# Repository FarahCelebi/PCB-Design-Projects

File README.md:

PCB Design Projects

A set of PCB designs built in KiCad, covering circuit fundamentals through to a complete USB-C powered environmental sensor system. Each project includes the full schematic, PCB layout, and the design reasoning behind key decisions — component selection, power regulation, signal integrity, and manufacturability.

Skills demonstrated

- Schematic capture, ERC, and footprint assignment
- PCB layout, routing, and Design Rules Checking (DRC)
- Current-limiting and Ohm's law-based component selection
- Decoupling capacitor strategy and power supply design (LDO regulation)
- Multi-layer (4-layer) stack-ups with dedicated GND/power planes
- I2C bus design, addressing, and pull-up resistor sizing
- USB-C power delivery, ESD protection, and differential pair routing
- Copper pours, thermal relief, and controlled-impedance routing
- Design for Manufacture (DFM): trace width selection, silkscreen clearance, panelization-aware board outlines
- Gerber generation and verification for fabrication

Projects
| # | Project | Description |
|---|---------|-------------|
| 01 | [LED Blink Circuit](./01-Led-Blink-Circuit) | Current-limited LED driver circuit with calculated resistor values for two different LED forward voltages. |
| 02 | [ATtiny85 Microcontroller Board](./02-ATtiny85-Microcontroller) | Minimal ATtiny85 breakout with a proper reset circuit, decoupling, and a ground plane, on a 2-layer board. |
| 03 | [AMS1117 Power Supply](./03-AMS1117-Power-Supply) | 5V-to-3.3V regulated power supply with proper input/output decoupling, built on a 4-layer stackup with dedicated GND/power planes. |
| 04 | [BME280 I2C Sensor Board](./04-BME280-I2C-Sensor) | Self-contained sensor module with onboard 5V-to-3.3V regulation, an ATtiny85, and a BME280 environmental sensor over I2C. |
| 05 | [USB-C Power Board](./05-USB-C-Power-Board) | USB-C input with ESD protection, CC detection, differential pair routing, and 3.3V regulation. |
| 06 | [IoT Environmental Monitor (Capstone)](./06-IoT-Environmental-Monitor) | Full system: USB-C input with ESD protection, onboard power regulation, an ATtiny85, and a BME280 sensor. Designed, fabricated, and assembled. |

Tools

- KiCad (schematic capture, PCB layout, DRC/ERC)

About this repository

Each project folder contains:
- A README with the design brief, schematic, PCB layout, and key decisions
- Schematic and PCB screenshots
- KiCad source files

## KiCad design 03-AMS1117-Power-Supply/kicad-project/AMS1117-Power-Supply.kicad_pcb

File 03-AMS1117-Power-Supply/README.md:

# AMS1117 Power Supply

A 5V-to-3.3V linear regulator board with full input/output decoupling,
built on a 4-layer stackup with dedicated ground and power planes.

## Schematic

## PCB Layout

## Design notes

- **Regulator:** AMS1117-3.3, a fixed 3.3V LDO. Input and output decoupling
  follow the datasheet's recommended pairing — a 10uF bulk capacitor for
  transient current demand alongside a 100nF capacitor for high-frequency
  noise, on both the input and output rails
- **Connectors:** J1 (input) and J2 (output) sit on opposite sides of the
  board, with the regulator in between — keeping the power path visually
  traceable left to right
- **PWR_FLAG:** placed on the +3.3V output rail and on GND, since both are
  externally driven/sourced rather than generated on this sheet, which
  satisfies KiCad's ERC for power rails with no visible source

## Stackup

This board uses a 4-layer stackup:

| Layer | Use |
|-------|-----|
| F.Cu | Component placement, signal/power routing |
| In1.Cu | Dedicated GND plane (solid pour) |
| In2.Cu | Dedicated power plane (solid pour)|
| B.Cu | Unused on this board — all routing fit on F.Cu |

A solid ground plane on an inner layer gives every trace on F.Cu a continuous,
low-impedance return path directly beneath it, which reduces EMI and noise
coupling compared to routing GND as traces on a single layer. For a simple
linear regulator like this, 2 layers would work fine electrically — this
board uses 4 specifically to establish and verify the stackup configuration,
via placement, and inner-layer pour workflow in KiCad.

## Manufacturing

- SMD throughout (SOT-223 regulator, 0805/0402 passives) for compact assembly
- Passed DRC with 0 violations, 0 unconnected nets
- Inner layer fills set to solid (not thermal relief) on small SMD pads

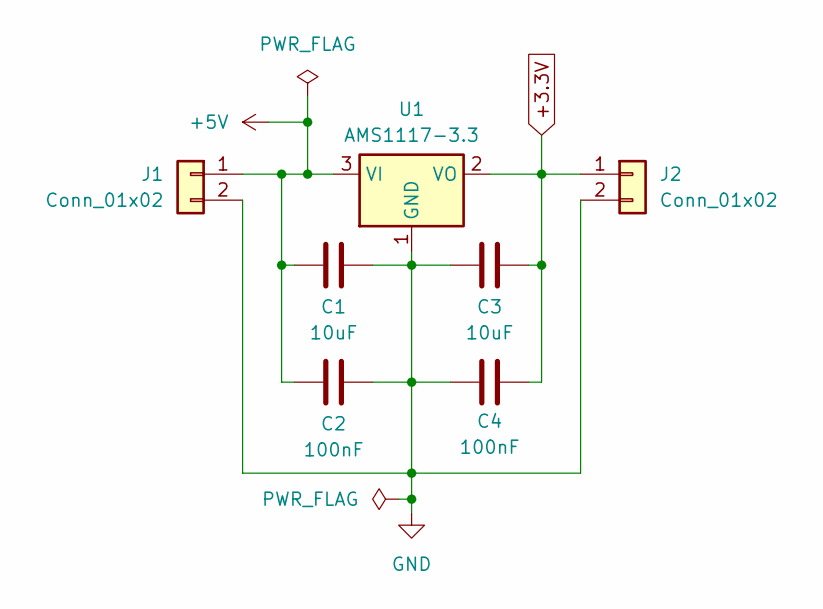
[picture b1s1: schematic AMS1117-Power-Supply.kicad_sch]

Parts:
C1, C3: 10uF; C_0805_2012Metric
C2, C4: 100nF; C_0402_1005Metric
J1, J2: Conn_01x02; PinHeader_1x02_P2.54mm_Vertical
U1: AMS1117-3.3; SOT-223-3_TabPin2

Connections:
+3.3V: C3.2, C4.2, J2.1, U1.2 (VO)
+5V: C1.2, C2.2, J1.1, U1.3 (VI)
GND: C1.1, C2.1, C3.1, C4.1, J1.2, J2.2, U1.1 (GND)

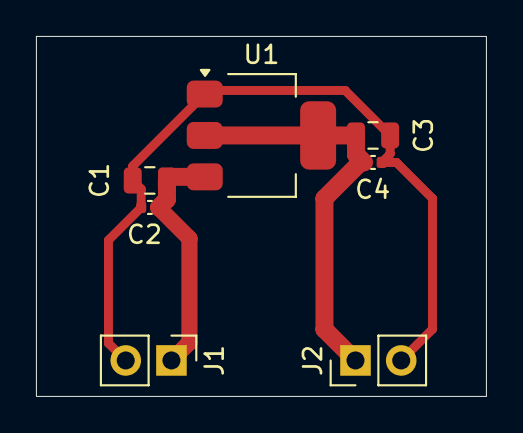
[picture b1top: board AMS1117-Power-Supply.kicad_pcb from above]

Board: 4 copper layers, 25.0 x 20.0 mm, 7 parts (0 on the bottom side), 3 nets.

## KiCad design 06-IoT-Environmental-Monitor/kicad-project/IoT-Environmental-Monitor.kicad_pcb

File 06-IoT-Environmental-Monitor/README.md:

# IoT Environmental Monitor

A complete, USB-C powered environmental sensor system: USB-C input with ESD
protection, onboard 3.3V regulation, an ATtiny85 microcontroller, and a
BME280 sensor reading temperature, humidity, and pressure over I2C. 

## Schematic

## PCB Layout

## Design notes

This board integrates four functional stages into one system:

**USB-C input + ESD:** the connector's CC1/CC2 pins are each pulled to GND
through a 5.1kΩ resistor, the minimum circuit needed for the board to be
recognized as a power sink and offered 5V. A USBLC6-2SC6 sits within a few
millimeters of the connector, clamping any electrostatic discharge spike
before it reaches the rest of the circuit. D+/D- run as a length- and
width-matched pair from the connector to the ESD IC.

**Power supply:** an AMS1117-3.3 regulates the incoming VBUS (5V) down to
3.3V, with standard input/output decoupling (10uF + 100nF on each side).

**ATtiny85 + I2C:** the standard MCU support circuit — 100nF decoupling, a
10kΩ RESET pull-up with a manual reset button, and 4.7kΩ pull-ups on the I2C
bus (SDA/SCL).

**BME280 sensor:** SDO is tied to GND through a 10kΩ resistor (setting the
I2C address to 0x76, per the datasheet's recommendation over a direct tie),
CSB is held high to select I2C mode over SPI, and VDD/VDDIO share the 3.3V
rail.

This is the same sensor circuit as the [BME280 I2C Sensor
Board](../04-bme280-i2c-sensor), with one key difference: that board only
accepts a 5V input on a generic 2-pin connector, while this board adds a full
USB-C input stage with CC detection and ESD protection — the difference
between a bench prototype and a board that could plug into any USB charger
or computer port.

## Layout

- Left-to-right signal flow: USB-C input → power regulation → ATtiny85 → BME280
- ESD protection IC and CC pull-downs clustered tightly around the USB-C
  connector
- D+/D- routed as a matched differential pair with no vias
- BME280 placed away from the regulator to avoid heat affecting readings
- Rectangular board outline sized to fit components with margin, keeping the
  board panelization-friendly (straight edges, no cutouts)

## Manufacturing

- 2-layer board, GND copper pour on the front copper layer
- Passed DRC with 0 violations, 0 unconnected nets

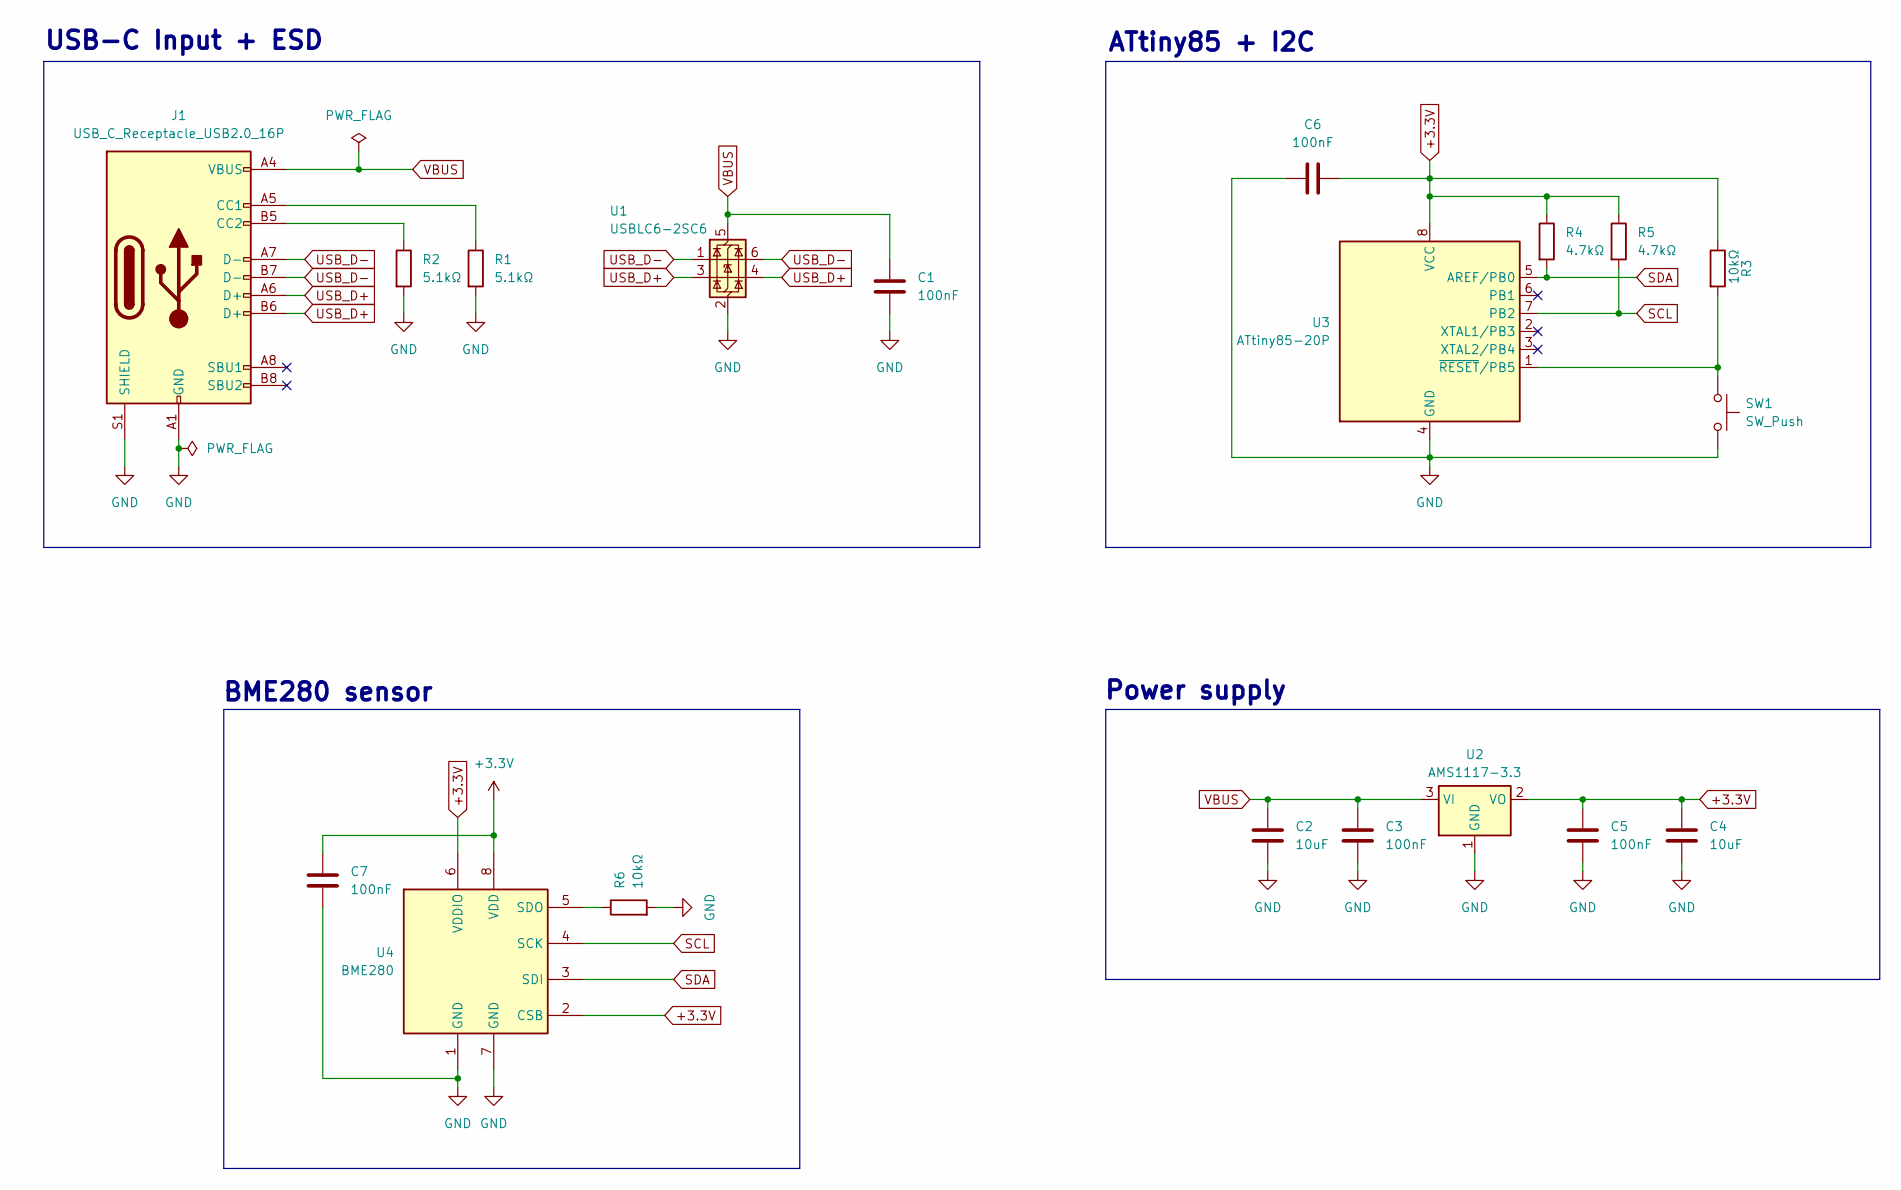
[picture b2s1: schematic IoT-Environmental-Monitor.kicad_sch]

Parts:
C1, C3, C5, C6, C7: 100nF; C_0402_1005Metric
C2, C4: 10uF; C_0805_2012Metric
J1: USB_C_Receptacle_USB2.0_16P; USB_C_Receptacle_HRO_TYPE-C-31-M-12
R1, R2: 5.1kΩ; R_0402_1005Metric
R3, R6: 10kΩ; R_0402_1005Metric
R4, R5: 4.7kΩ; R_0402_1005Metric
SW1: SW_Push; SW_PUSH_6mm
U1: USBLC6-2SC6; SOT-23-6
U2: AMS1117-3.3; SOT-223-3_TabPin2
U3: ATtiny85-20P; DIP-8_W7.62mm
U4: BME280; Bosch_LGA-8_2.5x2.5mm_P0.65mm_ClockwisePinNumbering

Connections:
+3.3V: C4.1, C5.1, C6.2, C7.1, R3.1, R4.1, R5.1, U2.2 (VO), U3.8 (VCC), U4.2 (CSB), U4.6 (VDDIO), U4.8 (VDD)
GND: C1.2, C2.2, C3.2, C4.2, C5.2, C6.1, C7.2, J1.A1 (GND), J1.A12 (GND), J1.B1 (GND), J1.B12 (GND), J1.S1 (SHIELD), R1.2, R2.2, R6.2, SW1.2, U1.2 (GND), U2.1 (GND), U3.4 (GND), U4.1 (GND), U4.7 (GND)
unnamed: J1.A5 (CC1), R1.1
unnamed: J1.B5 (CC2), R2.1
unnamed: R3.2, SW1.1, U3.1 (~RESET/PB5)
unnamed: R6.1, U4.5 (SDO)
SCL: R5.2, U3.7 (PB2), U4.4 (SCK)
SDA: R4.2, U3.5 (AREF/PB0), U4.3 (SDI)
USB_D+: J1.A6 (D+), J1.B6 (D+), U1.3 (I/O2), U1.4 (I/O2)
USB_D-: J1.A7 (D-), J1.B7 (D-), U1.1 (I/O1), U1.6 (I/O1)
VBUS: C1.1, C2.1, C3.1, J1.A4 (VBUS), J1.A9 (VBUS), J1.B4 (VBUS), J1.B9 (VBUS), U1.5 (VBUS), U2.3 (VI)

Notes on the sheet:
Power supply
BME280 sensor
ATtiny85 + I2C
USB-C Input + ESD

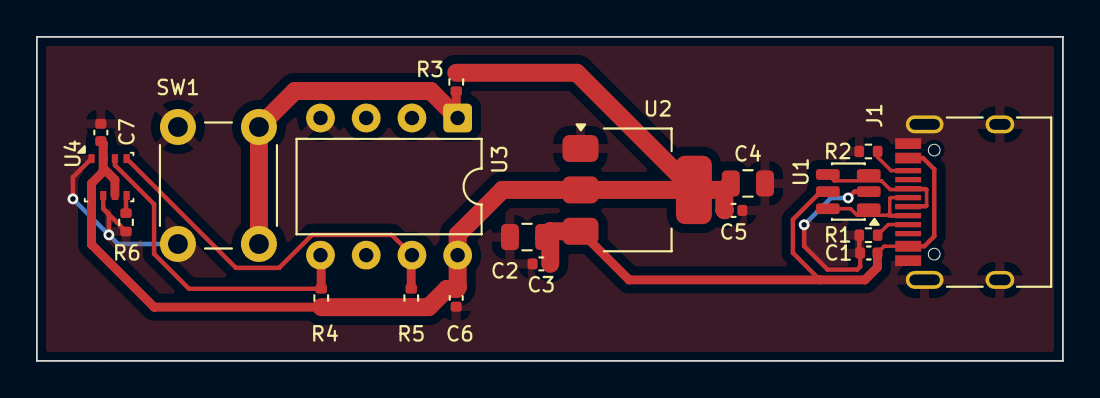
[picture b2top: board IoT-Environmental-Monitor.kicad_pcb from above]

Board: 2 copper layers, 57.0 x 18.0 mm, 19 parts (0 on the bottom side), 11 nets.

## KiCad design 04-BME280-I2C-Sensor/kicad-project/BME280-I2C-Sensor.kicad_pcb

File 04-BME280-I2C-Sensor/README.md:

# BME280 I2C Sensor Board

A self-contained environmental sensor board: takes 5V in, regulates it down
to 3.3V onboard, and reads temperature, humidity, and pressure from a BME280
over I2C via an ATtiny85.

## Schematic

## PCB Layout

## Design notes

**Power supply:** an AMS1117-3.3 regulates the 5V input down to 3.3V on board,
with the standard input/output decoupling pair (10uF + 100nF) on each side.
This makes the board self-contained — it only needs a 5V source, not a
pre-regulated 3.3V rail.

**I2C bus:** SDA and SCL run between the ATtiny85 (PB0/PB2) and the BME280,
each pulled up to 3.3V through a 4.7kΩ resistor. I2C uses open-drain
signaling, so the bus relies on these external pull-ups to return the line to
a high state — without them, both lines would float and communication would
fail.

**I2C address selection:** the BME280's SDO pin is tied to GND through a 10kΩ
resistor rather than wired directly, setting the device address to 0x76. A
direct connection works electrically the same way, but the datasheet
recommends a resistor since SDO can act as an output in some modes, and a
hard tie to GND would risk a short if that ever occurred.

**VDDIO:** the BME280 has separate VDD and VDDIO pins for its analog supply
and digital I/O supply. Both are tied to the same 3.3V rail here since the
whole board runs on a single voltage.

**Decoupling:** the ATtiny85, BME280, and AMS1117 each have capacitors placed
close to their respective power pins.

## Layout

- Three-stage left-to-right layout: power input/regulation → ATtiny85 → BME280
- BME280 placed away from the AMS1117 to avoid regulator heat skewing
  temperature readings
- Small SMD/LGA pads (BME280, 0402 passives) use solid zone connections
  rather than thermal relief spokes, since these pads are reflow-soldered in
  production and don't need the heat isolation thermal relief provides for
  hand soldering
- Some routing falls back to the back copper layer where two nets would
  otherwise cross on the front layer

## Manufacturing

- 2-layer board with GND copper pour
- Passed DRC with 0 violations, 0 unconnected nets

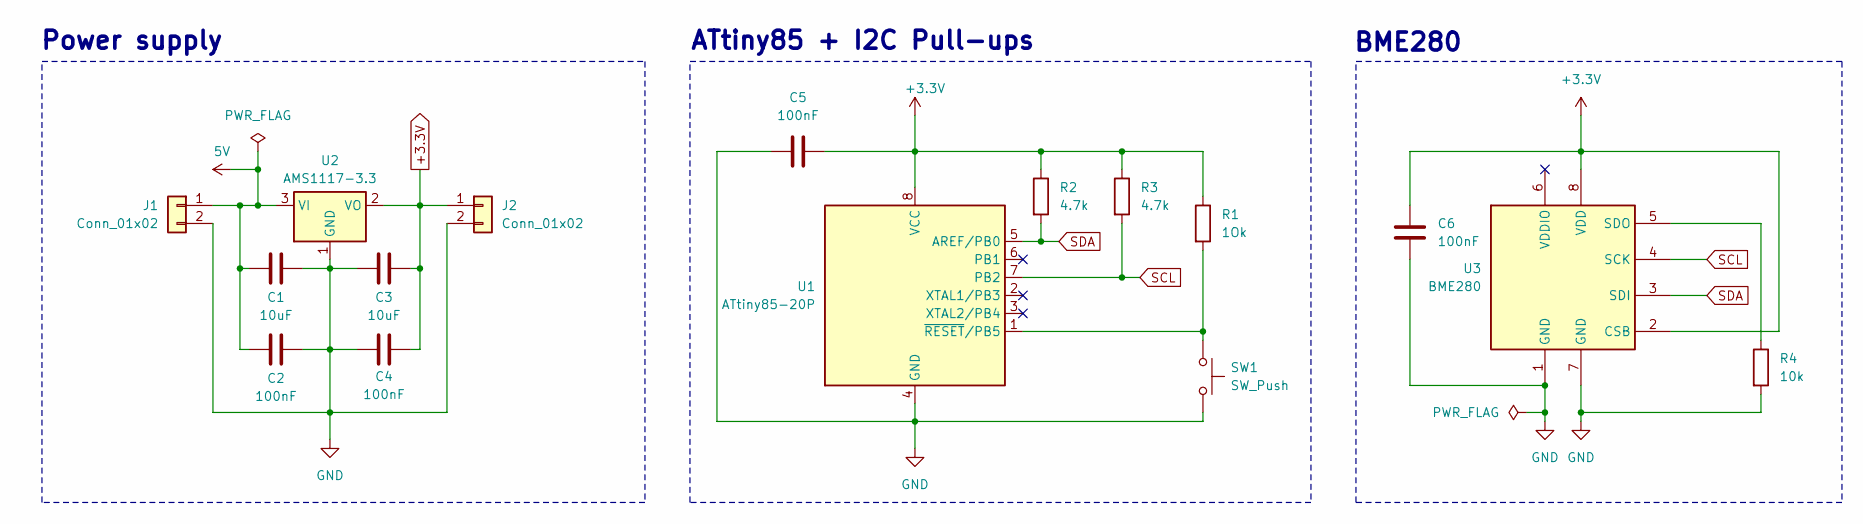
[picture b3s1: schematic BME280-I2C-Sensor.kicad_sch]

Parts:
C1, C3: 10uF; C_0805_2012Metric
C2, C4, C5, C6: 100nF; C_0402_1005Metric
J1, J2: Conn_01x02; PinHeader_1x02_P2.54mm_Vertical
R1: 1Ok; R_0402_1005Metric
R2, R3: 4.7k; R_0402_1005Metric
R4: 10k; R_0402_1005Metric
SW1: SW_Push; SW_PUSH_6mm
U1: ATtiny85-20P; DIP-8_W7.62mm
U2: AMS1117-3.3; SOT-223-3_TabPin2
U3: BME280; Bosch_LGA-8_2.5x2.5mm_P0.65mm_ClockwisePinNumbering

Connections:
5V: C1.2, C2.2, J1.1, U2.3 (VI)
+3.3V: C3.2, C4.2, C5.2, C6.1, J2.1, R1.1, R2.1, R3.1, U1.8 (VCC), U2.2 (VO), U3.2 (CSB), U3.8 (VDD)
GND: C1.1, C2.1, C3.1, C4.1, C5.1, C6.2, J1.2, J2.2, R4.2, SW1.2, U1.4 (GND), U2.1 (GND), U3.1 (GND), U3.7 (GND)
unnamed: R1.2, SW1.1, U1.1 (~RESET/PB5)
unnamed: R4.1, U3.5 (SDO)
SCL: R3.2, U1.7 (PB2), U3.4 (SCK)
SDA: R2.2, U1.5 (AREF/PB0), U3.3 (SDI)

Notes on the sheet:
BME280
Power supply
ATtiny85 + I2C Pull-ups

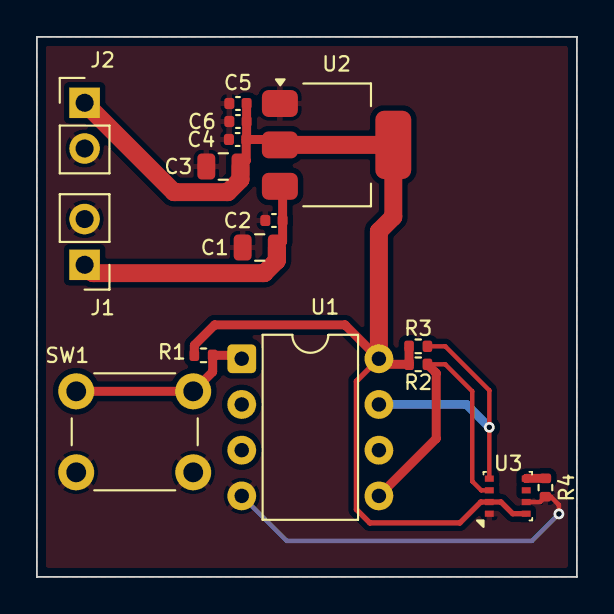
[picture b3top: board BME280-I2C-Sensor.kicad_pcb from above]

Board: 2 copper layers, 30.0 x 30.0 mm, 16 parts (0 on the bottom side), 7 nets.

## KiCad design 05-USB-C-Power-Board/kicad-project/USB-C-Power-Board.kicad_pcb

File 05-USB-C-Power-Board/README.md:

# USB-C Power Board

A USB-C input stage with ESD protection and onboard 3.3V regulation —
a complete, standards-compliant power entry point for a USB-powered design.

## Schematic

## PCB Layout

## Design notes

**USB-C power detection:** CC1 and CC2 are each pulled down to GND through a
5.1kΩ resistor. This is the minimum circuit required for a USB-C device to be
recognized as a power sink and offered 5V — without these pull-downs, a
USB-C source has no way to detect that something is plugged in.

**ESD protection:** a USBLC6-2SC6 sits within a few millimeters of the
connector, ahead of every other component on the board. Its job is to clamp
any electrostatic discharge spike before it can travel further into the
circuit — placing it anywhere else would leave the path between the
connector and the IC itself unprotected.

**Differential pair routing:** D+ and D- are routed as a matched pair —
equal length, equal width (0.2mm), routed together with no vias — to
maintain the 90Ω differential impedance USB 2.0 requires. Mismatched lengths
or widths here can cause signal reflections and data errors at the receiver.

**Power regulation:** VBUS (5V from the USB-C connector) feeds an AMS1117-3.3
to produce a regulated 3.3V output, available on a separate 2-pin connector
for downstream use.

## Layout

- ESD protection IC, CC pull-downs, and their decoupling cap are clustered
  tightly around the USB-C connector
- D+/D- routed as a matched differential pair directly from the connector to
  the ESD IC, with no other signals routed nearby to avoid coupling
- Power regulation stage placed downstream, since it carries no
  high-speed/impedance-sensitive signals and has more routing flexibility

## Manufacturing

- 2-layer board with GND copper pour
- Passed DRC with 0 violations, 0 unconnected nets

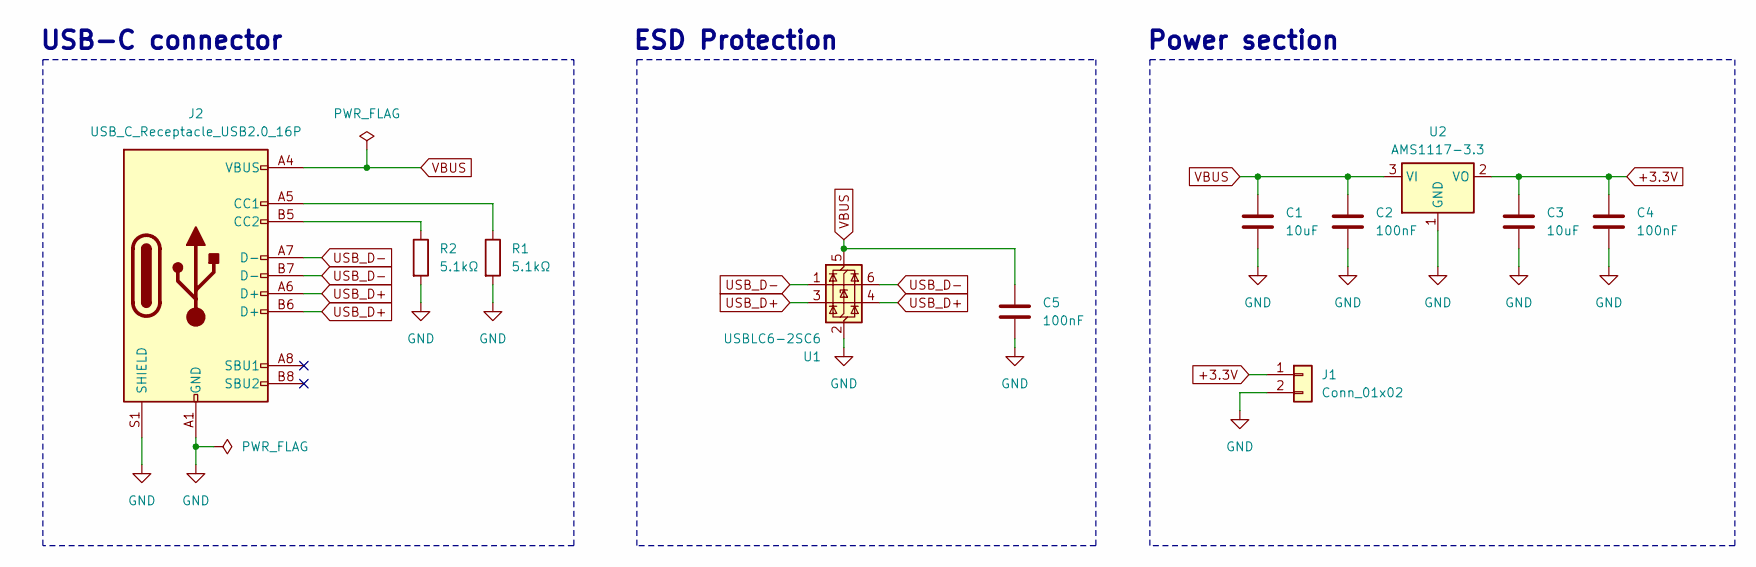
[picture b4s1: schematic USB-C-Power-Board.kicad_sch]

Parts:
C1, C3: 10uF; C_0805_2012Metric
C2, C4, C5: 100nF; C_0402_1005Metric
J1: Conn_01x02; PinHeader_1x02_P2.54mm_Vertical
J2: USB_C_Receptacle_USB2.0_16P; USB_C_Receptacle_HRO_TYPE-C-31-M-12
R1, R2: 5.1kΩ; R_0402_1005Metric
U1: USBLC6-2SC6; SOT-23-6
U2: AMS1117-3.3; SOT-223-3_TabPin2

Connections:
+3.3V: C3.1, C4.1, J1.1, U2.2 (VO)
GND: C1.2, C2.2, C3.2, C4.2, C5.2, J1.2, J2.A1 (GND), J2.A12 (GND), J2.B1 (GND), J2.B12 (GND), J2.S1 (SHIELD), R1.2, R2.2, U1.2 (GND), U2.1 (GND)
unnamed: J2.A5 (CC1), R1.1
unnamed: J2.B5 (CC2), R2.1
USB_D+: J2.A6 (D+), J2.B6 (D+), U1.3 (I/O2), U1.4 (I/O2)
USB_D-: J2.A7 (D-), J2.B7 (D-), U1.1 (I/O1), U1.6 (I/O1)
VBUS: C1.1, C2.1, C5.1, J2.A4 (VBUS), J2.A9 (VBUS), J2.B4 (VBUS), J2.B9 (VBUS), U1.5 (VBUS), U2.3 (VI)

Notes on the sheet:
ESD Protection
USB-C connector
Power section

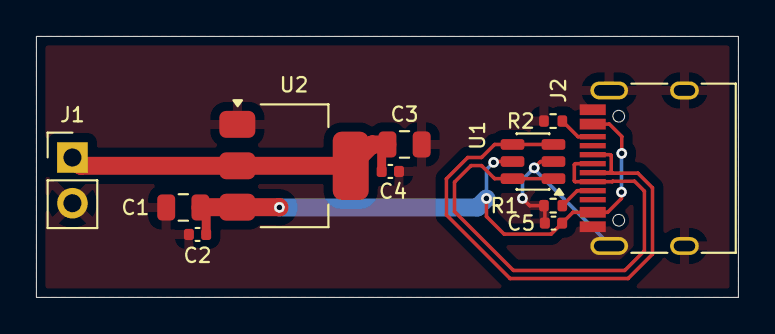
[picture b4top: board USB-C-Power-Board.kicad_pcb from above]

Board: 2 copper layers, 39.0 x 14.5 mm, 11 parts (0 on the bottom side), 7 nets.

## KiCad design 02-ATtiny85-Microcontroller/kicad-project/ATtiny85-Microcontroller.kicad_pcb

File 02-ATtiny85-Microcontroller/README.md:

# ATtiny85 Microcontroller Board

A minimal ATtiny85 breakout with a proper reset circuit, power decoupling, and
a ground plane poured on a 2-layer board.

## Schematic

## PCB Layout

## Design notes

The board follows the standard MCU support pattern used across virtually
every microcontroller design:

- **Decoupling:** a 100nF ceramic capacitor sits directly on VCC/GND, placed
  within 2mm of the chip's power pin to suppress switching noise from the
  digital logic
- **Reset:** a 10kΩ pull-up holds RESET high during normal operation; a
  momentary push button pulls it low for a manual reset. Without the pull-up,
  RESET would float and the chip could reset unpredictably from noise
- **Unused I/O:** all unused GPIO pins are explicitly marked no-connect at the
  schematic level, so anyone reviewing the design knows they were left
  unconnected on purpose, not by oversight

## Manufacturing

- Through-hole DIP-8 package for easy hand assembly and prototyping
- 2-layer board with a ground plane poured on the front copper layer
- Passed DRC with 0 violations, 0 unconnected nets
- Ground plane poured with solid connection on small-pad components

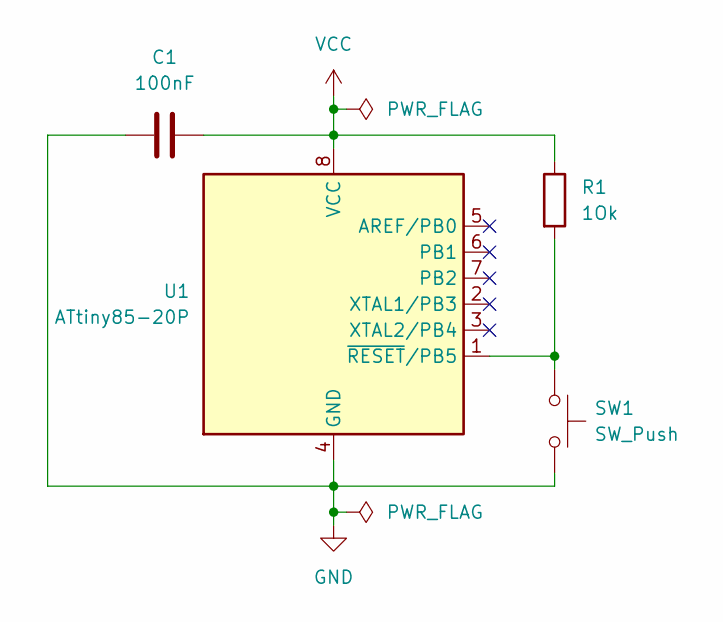
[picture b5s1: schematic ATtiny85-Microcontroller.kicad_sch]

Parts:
C1: 100nF; C_0805_2012Metric
R1: 1Ok; R_0805_2012Metric
SW1: SW_Push; SW_Push_SPST_NO_Alps_SKRK
U1: ATtiny85-20P; DIP-8_W7.62mm

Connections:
GND: C1.1, SW1.2, U1.4 (GND)
unnamed: R1.2, SW1.1, U1.1 (~RESET/PB5)
VCC: C1.2, R1.1, U1.8 (VCC)

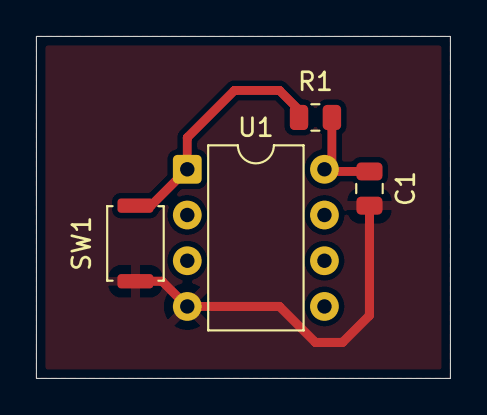
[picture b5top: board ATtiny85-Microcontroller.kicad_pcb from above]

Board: 2 copper layers, 23.0 x 19.0 mm, 4 parts (0 on the bottom side), 3 nets.

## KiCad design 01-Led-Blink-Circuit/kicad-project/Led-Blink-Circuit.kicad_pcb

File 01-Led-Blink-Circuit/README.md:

# LED Blink Circuit

A current-limited LED driver circuit with two parallel branches, each sized for a
different LED forward voltage.

## Schematic

## PCB Layout

## Design notes

Two LEDs (red and blue) run in parallel off a shared 3.3V rail, each with its
own series resistor sized using Ohm's law against the LED's actual forward
voltage rather than a single generic value:

- **Red LED branch:** R = (3.3V − 2.0V) / 10mA → 150Ω
- **Blue LED branch:** R = (3.3V − 3.0V) / 10mA → 33Ω

Sizing each resistor individually avoids under-driving or over-driving either
LED — a flat "one resistor fits all" value would have left one of the two
either too dim or running outside its rated current.

## Layout

- Two-layer board with a ground plane poured on the front copper layer
- 45° trace routing throughout, no 90° corners
- Components placed with current-flow order preserved (resistor → LED → GND,
  top to bottom) for easy visual tracing of the circuit
- Routing favors a clean, traceable rectangular path (+3.3V across the top,
  GND across the bottom) over the shortest possible trace length. At this
  circuit's current draw (~10mA per branch), the added trace length has no
  meaningful electrical impact, so legibility was the deciding factor. A
  tighter, shorter-trace layout would be the better choice if this board were
  being optimized for production at volume

## Manufacturing

- 2-layer, standard FR4
- Passed DRC with 0 violations
- Gerbers generated and verified in a Gerber viewer prior to export

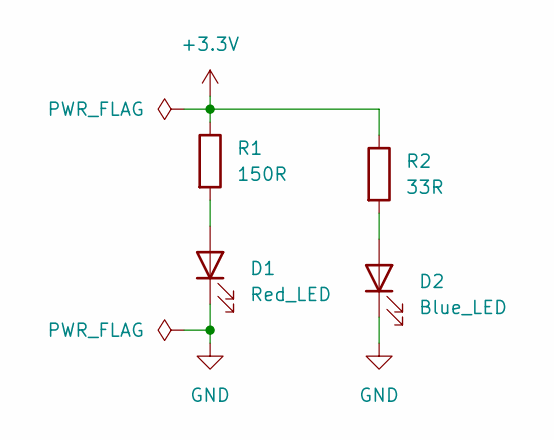
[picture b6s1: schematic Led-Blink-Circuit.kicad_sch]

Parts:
D1: Red_LED; D_0805_2012Metric
D2: Blue_LED; D_0805_2012Metric
R1: 150R; R_0805_2012Metric
R2: 33R; R_0805_2012Metric

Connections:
+3.3V: R1.1, R2.1
GND: D1.1 (K), D2.1 (K)
unnamed: D1.2 (A), R1.2
unnamed: D2.2 (A), R2.2

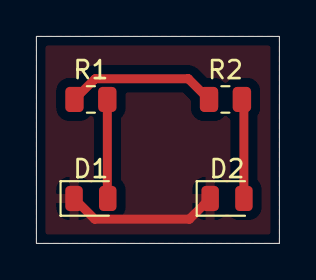
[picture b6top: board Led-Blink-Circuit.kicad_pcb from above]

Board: 2 copper layers, 13.5 x 11.5 mm, 4 parts (0 on the bottom side), 4 nets.

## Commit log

2026-06-21 Add repository overview and project index
    PCB designs spanning passive circuits, microcontroller boards, power regulation, I2C sensor integration, and USB-C power delivery — designed in KiCad.
2026-06-21 Add all six project write-ups, images, and source files
    Includes schematics, PCB layouts, and KiCad source files for all six boards, plus corrected project descriptions in the root README.
